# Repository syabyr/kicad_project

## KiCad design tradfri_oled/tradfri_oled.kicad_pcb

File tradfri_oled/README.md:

# tradfri_oled
support:
- I2C: SDA(PA0),SCL(PA1)
- VGM096064A5W01(SH1106G)(ADDR:)
- LIS3DH(ADDR:)
- LED_RABG(R:power,G:PF3,B:PF2),active low
- RESET Key
- SW1(PB13,default VCC)
- SW3(PB12,default VCC)

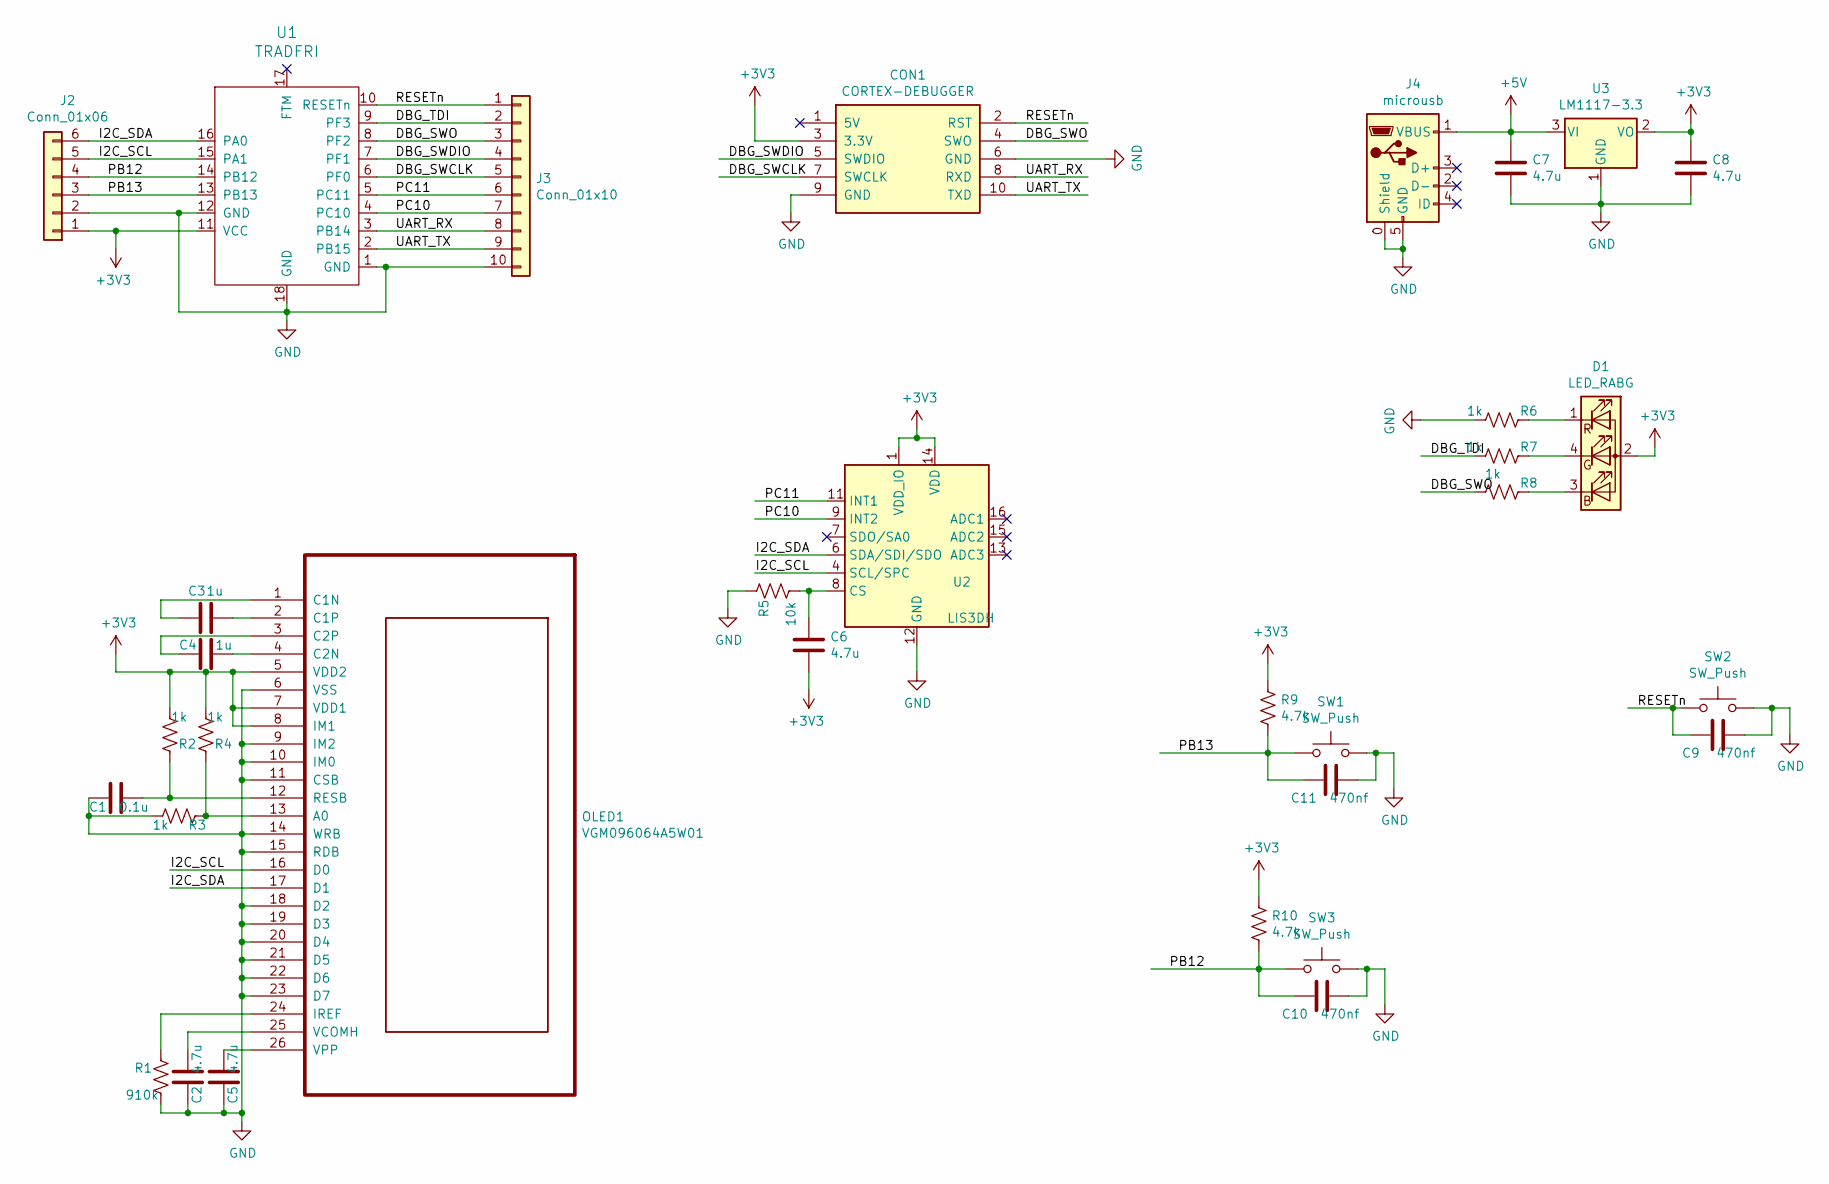
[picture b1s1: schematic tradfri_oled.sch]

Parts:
C1: 0.1u; C_0603_1608Metric_Pad1.05x0.95mm_HandSolder
C2, C5, C6: 4.7u; C_0603_1608Metric_Pad1.05x0.95mm_HandSolder
C3, C4: 1u; C_0603_1608Metric_Pad1.05x0.95mm_HandSolder
C7, C8: 4.7u; C_1206_3216Metric_Pad1.42x1.75mm_HandSolder
C9, C10, C11: 470nf; C_0603_1608Metric_Pad1.05x0.95mm_HandSolder
CON1: CORTEX-DEBUGGER; debugger_2x05_P1.27mm_Vertical
D1: LED_RABG; SMD020RGBC
J2: Conn_01x06; PinHeader_1x06_P2.54mm_Vertical
J3: Conn_01x10; PinHeader_1x10_P2.54mm_Vertical
J4: microusb; MICRO-USB_MICRO-USB-17
OLED1: VGM096064A5W01
R1: 910k; R_0603_1608Metric_Pad1.05x0.95mm_HandSolder
R2, R3, R4, R6, R7, R8: 1k; R_0402_1005Metric
R5: 10k; R_0402_1005Metric
R9, R10: 4.7k; R_0402_1005Metric
SW1, SW2, SW3: SW_Push; turtlekey
U1: TRADFRI
U2: LIS3DH; LGA-16_3x3mm_P0.5mm_LayoutBorder3x5y
U3: LM1117-3.3; SOT-223-LDO-1117LV

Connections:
+3V3: C6.2, C8.1, CON1.3 (3.3V), D1.2 (A), J2.1, OLED1.5 (VDD2), OLED1.7 (VDD1), OLED1.8 (IM1), R2.2, R4.2, R9.2, R10.2, U1.11 (VCC), U2.1 (VDD_IO), U2.14 (VDD), U3.2 (VO)
+5V: C7.1, J4.1 (VBUS), U3.3 (VI)
/DBG_SWCLK: CON1.7 (SWCLK), J3.5, U1.6 (PF0)
/DBG_SWDIO: CON1.5 (SWDIO), J3.4, U1.7 (PF1)
/DBG_SWO: CON1.4 (SWO), J3.3, R8.2, U1.8 (PF2)
/DBG_TDI: J3.2, R7.2, U1.9 (PF3)
/I2C_SCL: J2.5, OLED1.16 (D0), U1.15 (PA1), U2.4 (SCL/SPC)
/I2C_SDA: J2.6, OLED1.17 (D1), U1.16 (PA0), U2.6 (SDA/SDI/SDO)
/PB12: C10.2, J2.4, R10.1, SW3.1, U1.14 (PB12)
/PB13: C11.2, J2.3, R9.1, SW1.1, U1.13 (PB13)
/PC10: J3.7, U1.4 (PC10), U2.9 (INT2)
/PC11: J3.6, U1.5 (PC11), U2.11 (INT1)
/RESETn: C9.2, CON1.2 (RST), J3.1, SW2.1, U1.10 (RESETn)
/UART_RX: CON1.8 (RXD), J3.8, U1.3 (PB14)
/UART_TX: CON1.10 (TXD), J3.9, U1.2 (PB15)
GND: C1.1, C2.1, C5.1, C7.2, C8.2, C9.1, C10.1, C11.1, CON1.6 (GND), CON1.9 (GND), J2.2, J3.10, J4.0 (Shield), J4.5 (GND), OLED1.6 (VSS), OLED1.9 (IM2), OLED1.10 (IM0), OLED1.11 (CSB), OLED1.14 (WRB), OLED1.15 (RDB), OLED1.18 (D2), OLED1.19 (D3), OLED1.20 (D4), OLED1.21 (D5), OLED1.22 (D6), OLED1.23 (D7), R1.2, R3.2, R5.1, R6.2, SW1.2, SW2.2, SW3.2, U1.1 (GND), U1.12 (GND), U1.18 (GND), U2.5 (GND), U2.10 (GND), U2.12 (GND), U3.1 (GND)
unnamed: C1.2, OLED1.12 (RESB), R2.1
unnamed: C2.2, OLED1.25 (VCOMH)
unnamed: C3.1, OLED1.2 (C1P)
unnamed: C3.2, OLED1.1 (C1N)
unnamed: C4.1, OLED1.4 (C2N)
unnamed: C4.2, OLED1.3 (C2P)
unnamed: C5.2, OLED1.26 (VPP)
unnamed: C6.1, R5.2, U2.8 (CS)
unnamed: D1.1 (RK), R6.1
unnamed: D1.3 (BK), R8.1
unnamed: D1.4 (GK), R7.1
unnamed: OLED1.13 (A0), R3.1, R4.1
unnamed: OLED1.24 (IREF), R1.1

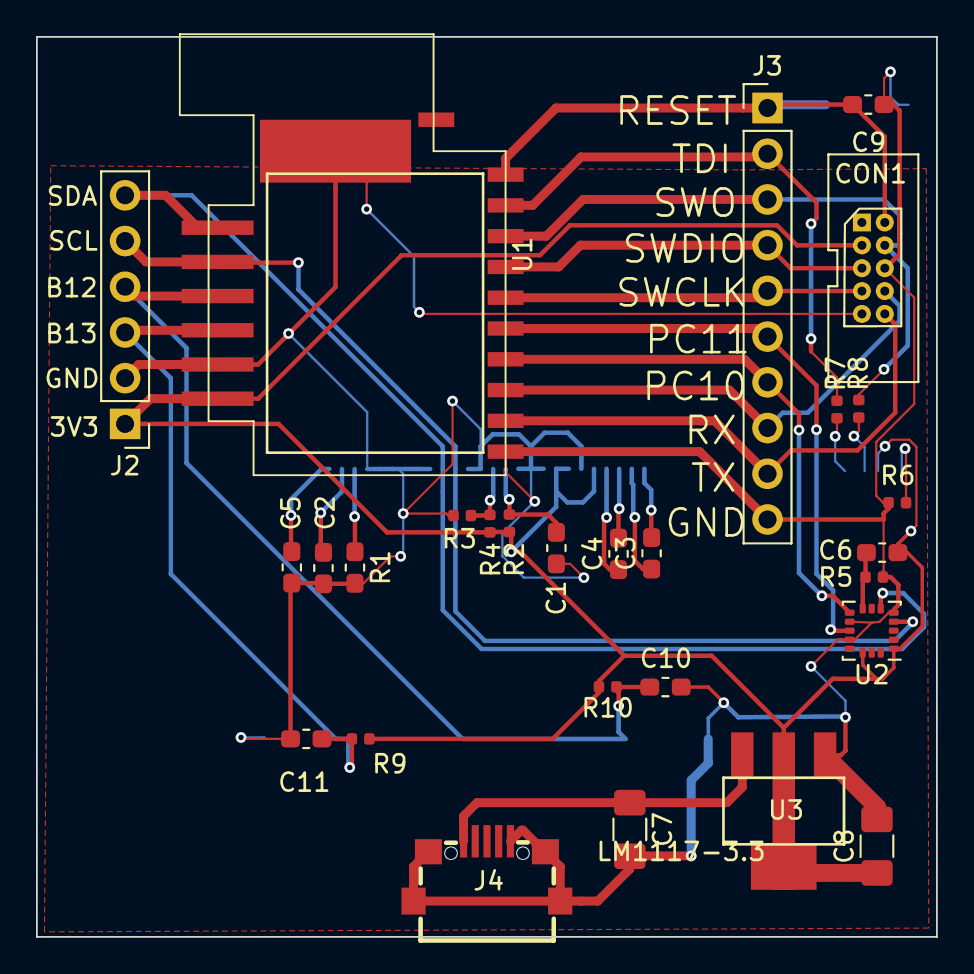
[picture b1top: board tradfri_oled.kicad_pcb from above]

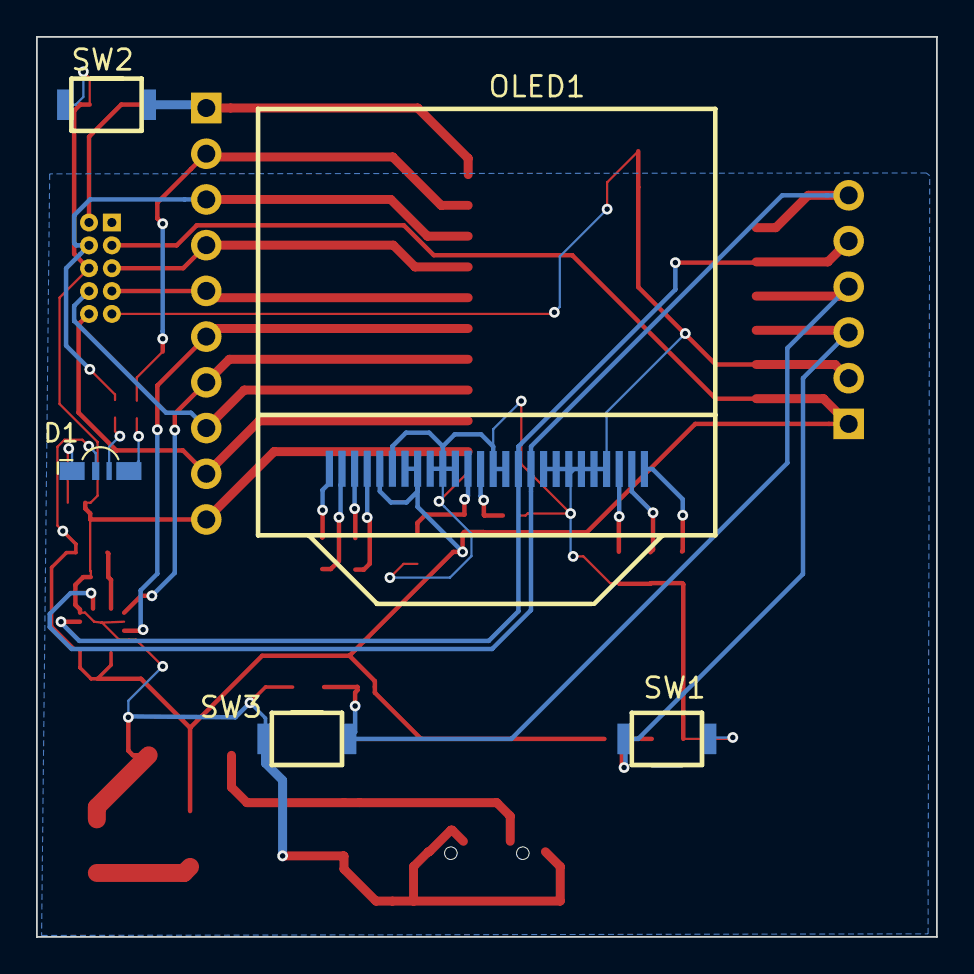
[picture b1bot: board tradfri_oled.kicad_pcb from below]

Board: 2 copper layers, 50.0 x 50.0 mm, 33 parts (4 on the bottom side), 29 nets.

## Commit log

2020-09-14 tradfri-oled
2020-09-15 20200914
2020-09-28 final
